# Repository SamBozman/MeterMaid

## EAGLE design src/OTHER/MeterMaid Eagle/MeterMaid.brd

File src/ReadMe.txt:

This version of the (yet) uncompleted Metermaid is going to be using ArduinoJson 6.
Version MM_nodeR_V4.2 was using ArduinoJson 5. 
Eventually I plan to merging this copy (MM_nodeR_5.x) with
the master MM_nodeR_V4.2

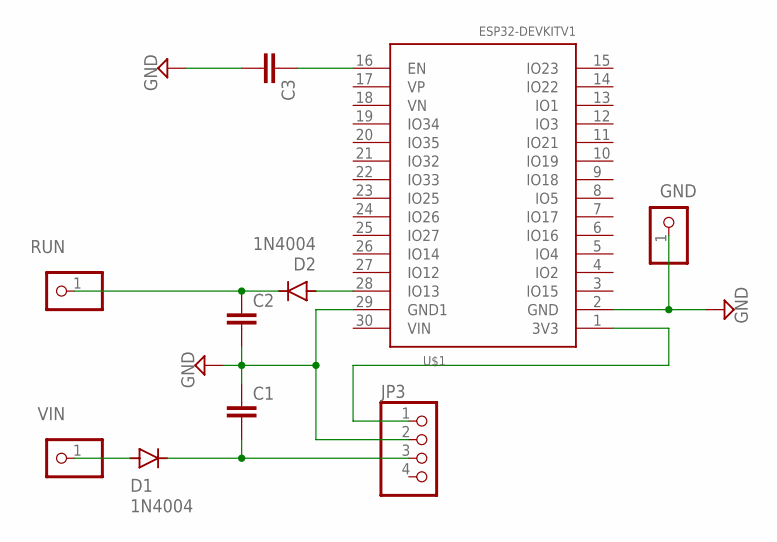
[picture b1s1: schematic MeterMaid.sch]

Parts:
C1, C2, C3: C-EU025-050X050; C025-050X050
D1, D2: 1N4004; DO41-10
GND: PINHD-1X1; 1X01
JP3: PINHD-1X4; 1X04
RUN: PINHD-1X1; 1X01
U$1: ESP32DEVKITV1; ESP32-DEVKITV1
VIN: PINHD-1X1; 1X01

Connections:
GND: C1.1, C2.2, C3.2, GND.1, JP3.2, U$1.2 (GND), U$1.29 (GND1)
unnamed: JP3.1, U$1.1 (3V3)
unnamed: C1.2, D1.C, JP3.3
unnamed: D2.A, U$1.28 (IO13)
unnamed: C2.1, D2.C, RUN.1
unnamed: C3.1, U$1.16 (EN)
VIN: D1.A, VIN.1

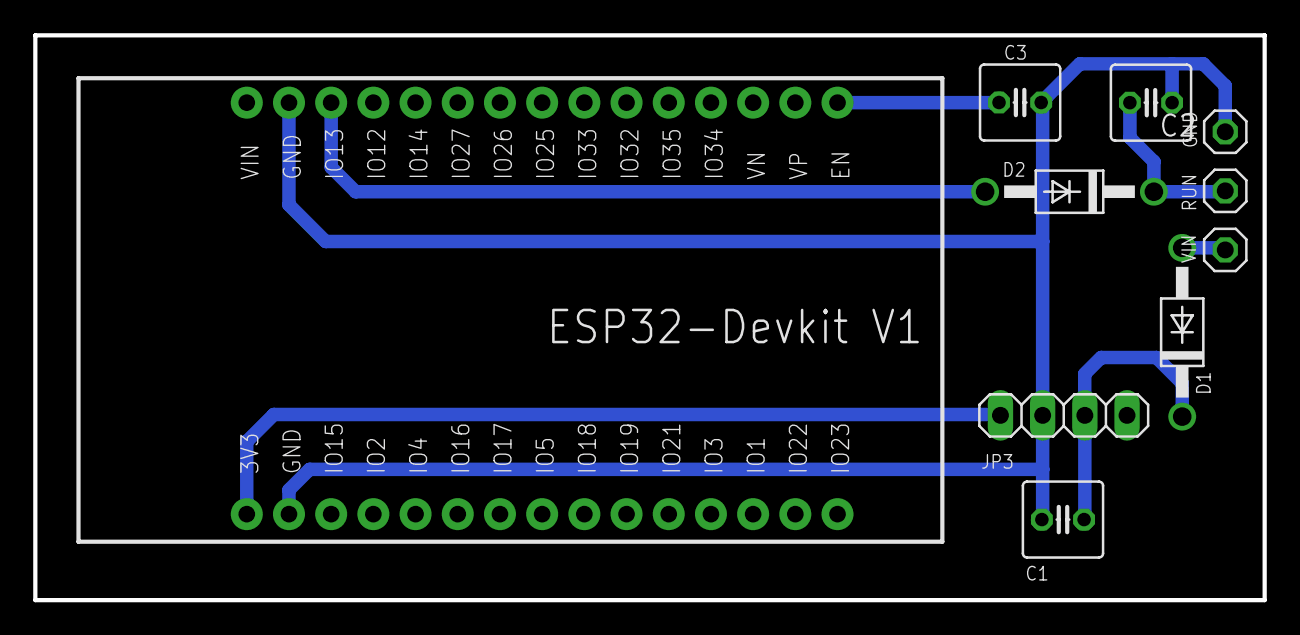
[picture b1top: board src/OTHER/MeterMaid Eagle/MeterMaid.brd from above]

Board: 2 copper layers, 74.0 x 34.0 mm, 10 parts (0 on the bottom side), 7 nets.

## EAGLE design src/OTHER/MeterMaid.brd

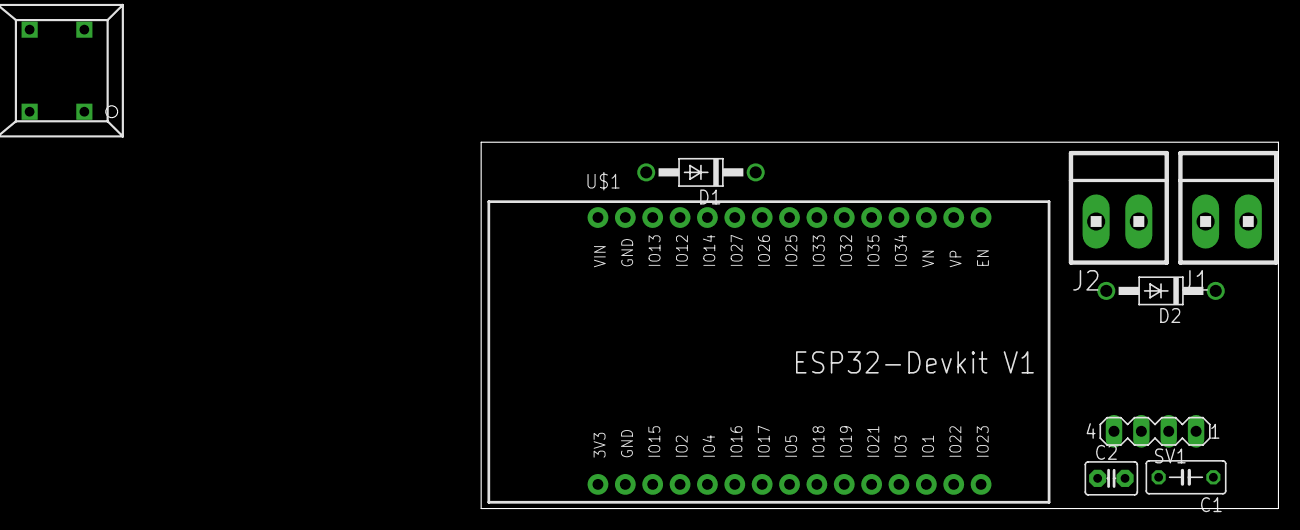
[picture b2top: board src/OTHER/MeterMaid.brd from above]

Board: 2 copper layers, 74.0 x 34.0 mm, 9 parts (0 on the bottom side), 7 nets, no tracks yet.

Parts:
AP_SW: 5501
C1: 33uf, 50V; C050-030X075
C2: .01 uf; C2.5-3
D1, D2: 1N4004; DO41-10
J1, J2: 1X2MTA
SV1: D24V5F5; MA04-1
U$1: ESP32DEVKITV1; ESP32-DEVKITV1

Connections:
5V_IN: C2.2, SV1.4, U$1.30
GND: AP_SW.NO, C1.2, C2.1, SV1.3, U$1.2, U$1.28
unnamed: D1.C, J1.2
unnamed: D2.A, J2.2
PIN13: D1.A, U$1.28
PIN25: AP_SW.1A, U$1.23
VIN: C1.1, D2.C, SV1.2

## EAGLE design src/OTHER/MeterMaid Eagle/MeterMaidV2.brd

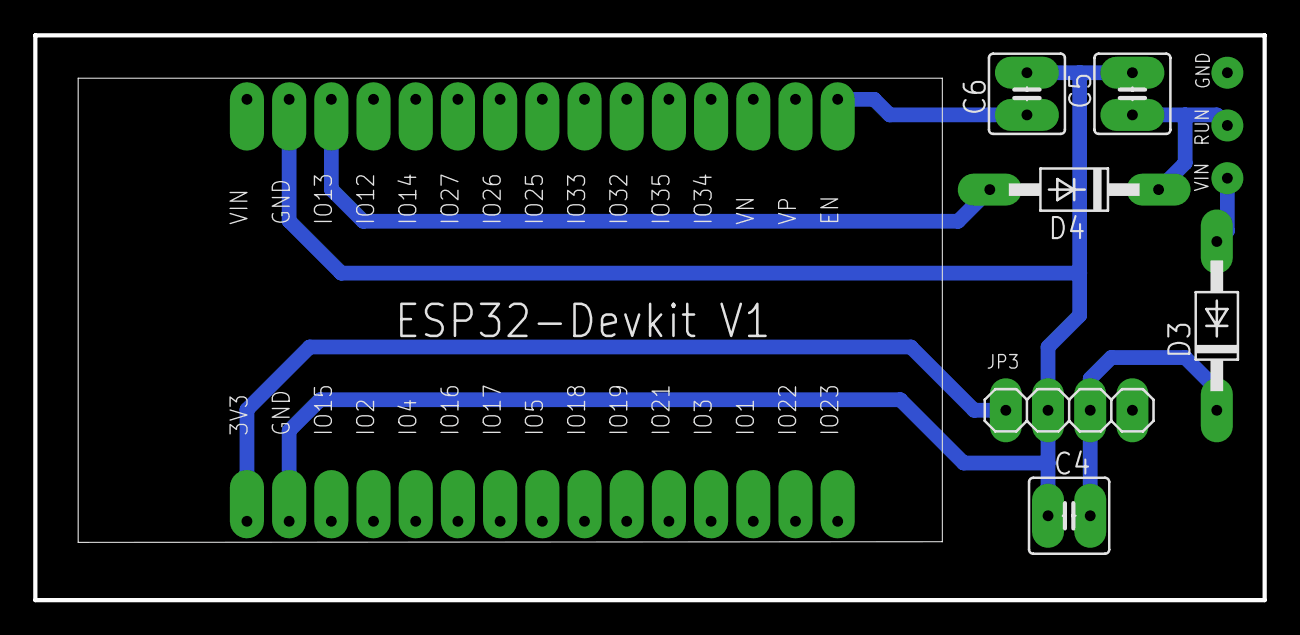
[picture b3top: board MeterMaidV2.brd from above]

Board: 2 copper layers, 74.0 x 34.0 mm, 10 parts (0 on the bottom side), 7 nets.

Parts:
C4: 47uf; C025-050X050
C5, C6: 100nf; C025-050X050
D3, D4: 1N4004; DO41-10
GND: 1X01LP
JP3: 1X04
RUN: 1X01LP
U$1: ESP32-DEVKITV2
VIN: 1X01LP

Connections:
GND: C4.1, C5.2, C6.1, GND.P$1, JP3.2, U$1.2, U$1.29
unnamed: JP3.1, U$1.1
unnamed: C4.2, D3.C, JP3.3
unnamed: D4.A, U$1.28
unnamed: C5.1, D4.C, RUN.P$1
unnamed: C6.2, U$1.16
unnamed: D3.A, VIN.P$1

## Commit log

2019-10-27 Added MQTT abilities
2019-11-04 Re-Staged
2019-11-09 Deleted Char Conversion function
2019-11-09 Removed experimental ConCat function
2019-11-09 Added an example of a working concatenator
2019-11-10 Moved includes file into delarations
2019-12-10 Cleaned Up Code
2019-12-10 Declared new function
2019-12-10 Removed shouldSaveConfig
2019-12-10 Repaired code
2019-12-10 TEST
2019-12-19 Fixed noConfig problem
2019-12-23 Created char array from dataInCallback.
2019-12-24 Reverted
2019-12-24 New branch to develop with ArduinoJson 6
2019-12-27 Rewrote Json code to reflect new ArduinoJason 6
2019-12-27 Tried to format ArduinoJson properly
2020-01-02 Cleaning up code
2020-01-04 dataCallBack working with manual payload but so far not working with byte payload
2020-01-06 Fixed error in callback
2020-01-06 dataInCallback function now working properly
2020-01-06 Added Node-Red flow
2020-01-08 Minor code fixes
2020-01-08 Minor code optimization
2020-01-09 Fixed code in Setup
2020-01-09 Rewrote addToHM() and goToSleep()
2020-01-09 Added Millis example in a text file
2020-01-09 Moved Global variables out of setup() into declarations.h
2020-01-10 Rewrote mqttClient connection routine
2020-01-17 Added get date function
2020-01-25 Revamped getConfig
2020-01-25 Minor repairs
2020-01-28 Partially completed checkPmiDue() function
2020-02-02 Check PMI function completed but not tested
2020-02-12 Finished. Various housekeeping tasks to complete.
2020-02-19 Minior Changes
2020-02-25 Revised WiFi control
2020-02-29 Teaked WiFi setup
2020-03-04 All publish sequences set up. Test needed
2020-03-06 Finished basic operation. Works but more needed
2020-06-09 OTHER additions
2020-12-23 Added Includes
2020-12-23 Added other documents
2021-01-02 Added extra documents
2021-01-03 Made a change to setup.h. (correct?)
2021-01-26 Removed old files
2021-01-28 Removed Static DNS settings
2021-02-06 Initial Working
2021-02-06 Setup ClientID to use full MacAddress
2021-02-11 Repaired getConfig function
2021-02-11 Minor code tweaks...
2021-02-18 Pre-reWrite
2021-02-18 Repaired incorrect char arrays
2022-10-18 Added new libraries
